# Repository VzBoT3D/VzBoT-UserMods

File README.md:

# VzBoT UserMods repository

Welcome to the VzBoT UserMods repository, here you may find community mods for the VzBoT 3D-printer.

*Remember to update this README when uploading new mod!*

There is a [contributing guide available here](./CONTRIBUTING.md).

## Directory structure

Create a folder containing your name (without spaces) and create a folder for your mod(s).

Suggested directory layout for your mod:
- creator_name/
  - mod_name/
    - README.md with a description, optionally build instructions and required parts
    - stl/ folder with stereolithographical models, oriented correctly for printing
    - cad/ folder with original design files (STEP, F3D, Scad, etc.) (optional)
    - doc/ folder with supported documentation (optional)
    - images/ folder with screen shots/renders/etc.

## Table structure

Update the following table with the information about your mod:
- Your name
- A link to your sub-folder
- A short description of your mod
- The build difficulty:
  - :green_heart: for :green_heart: (Easy)
  - :blue_heart: for :blue_heart: (Intermediate)
  - :heart: for :heart: (Advanced)

like so:
`
| Creator | [Mod title](link) | ✔️/✖️ | ✔️/✖️ | Description | Difficulty `

---

## Mods

| Creator | Mod title | Description | [Vz330](https://github.com/VzBoT3D/VzBoT-Vz330) | [Vz235](https://github.com/VzBoT3D/VzBoT-Vz235) | Difficulty
| --- | --- | --- | --- | --- | --- |
| example    | [Example mod](./creator_here/mod_folder_name)| Example entry for the table | ✔️ | ✔️ | :green_heart::blue_heart::heart: |
| airox    | [VZ235 Tophat](./airox/vz235_tophat)| A tophat for the vz235 | ✖️ | ✔️ | :green_heart: |
| AdderMk2   | [Patch_Cura](./AdderMk2/Patch_Cura) | Updates 2020 Tronxy profiles in Cura | ✔️ | ✔️ | :blue_heart: |
| CapnKrunchy | [Aluminum Z WAGO Mount](./CapnKrunchy/Aluminum_Z_WAGO_Mount) | WAGO mount for Aluminum Z bed assembly | ✔️ | ✖️ | :green_heart: |
| catalinutzz| [Hemera mount](./catalinutzz/hemera-mount) | Hemera mount for the VZ Printhead | ✔️ | ✔️ | :green_heart: |
| ckvsoft    | [CPAP_back_panel_tube_mount_VZ330](./ckvsoft/CPAP_back_panel_tube_mount_VZ330)| CPAP back panel tube mount VZ330. | ✔️ | ✖️ | :green_heart: |
| ckvsoft    | [WaveShare](./ckvsoft/waveshare_5inch_DSI_LCD)| WaveShare 5inch DSI LCD. | ✔️ | ✔️ | :green_heart: |
| der-pw    | [HBVCam-3M2111_corner-mount](./der-pw/HBVCam-3M2111_corner-mount)| HBVCam-3M2111 corner-mount | ✖️ | ✔️ | :green_heart: |
| edsped    | [Bowden Collet Adapter](./edsped/) | Bowden Collet Adapter  | ✔️ |  ✔️ | :green_heart: |
| EduardoMDSousa  | [Vz-Printhead Printed MGN12H](./EduardoMDSousa/Vz-Printhead-Printed-MGN12H) | VzPrinthead Printed MGN12H | ✔️ | ✔️ | :green_heart: |
|                 | [Vz-Printhead-Printed_Standoffs-MGN12](./EduardoMDSousa/Vz-Printhead-Printed_Standoffs-MGN12) | Vz-Printhead-Printed_Standoffs-MGN12 | ✔️ | ✔️ | :green_heart: |
|                 | [Vz-Printhead-Printed-MGN12H-Orbiter-1.5-Mood](./EduardoMDSousa/Vz-Printhead-Printed-MGN12H-Orbiter-1.5-Mood) | Vz-Printhead-Printed-MGN12H-Orbiter-1.5-Mood | ✔️ | ✔️ | :green_heart: |
| | [Vz-Printhead Printed Standoffs MGN12](./EduardoMDSousa/Vz-Printhead-Printed_Standoffs-MGN12) | Vz-Printhead Printed Standoffs MGN12 | ✔️ | ✔️ | :green_heart: |
|Glizzynator | [M4_Spool_Holder](./Glizzynator/M4_Spool_Holder)| Modifies the spool holder to use M4 screws instead of M3 | ✔️ | ✔️ | :green_heart: |
| jpbnto     | [Y endstop](./jpbnto/yendstop) | Y-endstop using the Tronxy XS5A switch | ✔️ | ✖️ | :green_heart: |
| | [VzHextrudort heavy back plate](./jpbnto/vzhextrudort_heavy_back_plate) | Y-endstop using the Tronxy XS5A switch | ✔️ | ✖️ | :green_heart: |
| jurisv      | [SLA CPAP Trihorn](./jurisv/sla_cpap_trihorn)                             | CPAP Trihorn Fan ducts for SLA printers as single piece          | ✔️ | ✖️ | :green_heart: |
| karnadi    | [NF Crazy front face](./karnadi/NF_Crazy_2510_BLTouch) | NF Crazy front face 2510 fan with BLTouch mount | ✔️ | ✔️ | :green_heart: |
|            | [VzHextrudort pneumatic coupler](./karnadi/VzHextrudort_pneumatic_coupler) | VzHextrudort pneumatic PTFE coupler | ✔️ | ✔️ | :green_heart: |
| keefo      | [vent hose adapter](./keefo/vent_hose_adapter) | vent hose adapter | ✔️ | ✖️ | :green_heart: |
| knarfie    | [12mm Linear Rod](./knarfie/12mm_rods) | Mod for 12mm linear rods | ✔️ | ✖️ | :green_heart: |
|            | [Idler Shoulder](./knarfie/shoulder_idler) | Idler mounts with spots for shoulder bolts  | ✔️ | ✖️ | :green_heart: |
|            | [Trihorn](./knarfie/trihorn_duct) | Trihorn duct for the VZ Printhead | ✔️ | ✔️ | :green_heart: |
| MadduxVape | [Vz330 Duet Config](./MadduxVape) | Vz330 AWD Config for Duett board| ✔️ |  ✖️ | :green_heart: |
| marbocub   | [Vz330 Y-Gantry-1515](./marbocub/Vz330_Y-Gantry-1515) | Vz330 Y-Gantry for 1515 size gantry | ✔️ |  ✖️ | :green_heart: |
| mdwasp     | [Swappable Exhaust Tube](./mdwasp/swappable_exhaust_tube) | Hot-swappable exhaust tube | ? | ✔️ | :green_heart: |
| panik988   | [Sherpa + NF Crazy front face (bracket)](./panik988/sherpa_nf_crazy_bracket) | NF Crazy Face Mount with bracket for Sherpa | ✔️ | ✔️ | :green_heart: |
| pbsuper    | [VZTrident](./pbsuper/VZTrident)| Tripple Z for VZbot complete printer. | ✔️ | ✔️ | :blue_heart: |
|            | [Quickdraw](./pbsuper/Quickdraw)| Quickdraw for Alu Printhead. | ✔️ | ✔️ | :green_heart: |
|            | [Brace_Dancer](./pbsuper/Brace_Dancer)| Brace for Dancer so Fanduct can't move sideways. | ✔️ | ✔️ | :green_heart: |
| Polar_Ted  | [VZ HextrudORT mount](./Polar_Ted/VZ_HextrudORT_High_Motor_Mount_for_EVA/) | VZ HextrudORT high motor mount for EVA print head and V6 hot end | ✔️ |  ✔️ | :green_heart: |
|            | [VZ Sexbolt Z Endstop](./Polar_Ted/Sexbolt_Sidepiece_Z_Switch/) | Sexbolt side mounted Z endstop for VZ bed frame  | ✔️ |  ✔️ | :green_heart: |
|            | [VZ 330 Skirt Set](./Polar_Ted/VZ330_skirt/ ) | VZ 3330 SKirt Set with V0 Display | ✔️ | ✖️ | :green_heart: |
|            | [X_Y_Pully_Height_Gauge](./Polar_Ted/X_Y_Pully_Height_Gauge/) | X Y pully height gauge  | ✔️ |  ✔️ | :green_heart: |
|            | [X_Y Motor Support](./Polar_Ted/X_Y_Motor_support/) | Support shelf for X and Y motors  | ✔️ |  ✔️ | :green_heart: |
| Rac        | [MGN9 Gantry](./Rac/MGN9_gantry) | MGN9 gantry | ✔️ | ✔️ | ✖️ | :blue_heart: |
| rilmar     | [X5SA Z](./rilmar/X5SA_Z) | X5SA Z | ✔️ | ✔️ | :green_heart: |
| RODAM 3D   | [180_Hinges](./RODAM_3D/180_Hinges/) | 180 Hinges for full door open  | ✖️ |  ✔️ | :green_heart: |
|            | [2WD_2_COLOR_SCREW_PACK](./RODAM_3D/2WD_2_COLOR_SCREW_PACK/) | 2 color Idler with mod for screw kit  | ✖️ |  ✔️ | :green_heart: |
| SFINAE     | [Rapido HF mount](./SFINAE/Rapido_HF_30mm_fan) | Rapido HF mount for 30mm fan | ✔️ | ✔️ | :green_heart: |
| Skysi      | [Beefy X-Endstop](./Skysi/Beefy%20X-Endstop) | Beefed up Enstop for X | ✔️ | ✔️ | :green_heart: |
| SSerpente  | [Klicky probe](./SSerpente/Klicky%20probe%20Vzbot) | Klicky probe mount | ✔️ | ✔️ | :green_heart: |
| treintjes  | [Skirt](./treintjes/VzBot_Skirt) | Skirt for the VZ-Bot to house electronics under the frame | ✔️ |  ✖️ | :green_heart: |
| MadduxVape | [Vz330_Duet_Config](./MadduxVape) | Vz330 AWD Config for Duett board| ✔️ |  ✖️ | :green_heart: |
| zxzimeng  | [12mm rod aligner](./zxzimeng/12mm_aligner/) | 12mm Z Rod Aligner  | ✖️ |  ✔️ | :green_heart: |
| Lobod     | [VzHextrudORT Optical Filament Sensor](./Lobod/VzHextrudORT_Filament-Sensor/) | Optical Filament sensor for printed VzHextrudORT | ✔️ | ✔️ | :heart: |

<sub>Credits to [VoronDesign/VoronUsers](https://github.com/VoronDesign/VoronUsers)</sub>

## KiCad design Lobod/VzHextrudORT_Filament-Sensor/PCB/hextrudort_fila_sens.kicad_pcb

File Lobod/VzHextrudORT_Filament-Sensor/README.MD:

# Better filament sensor for VzHextrudORT

Based on ERCF Binky and has the same BOM.
Uses similar principle as hall effect filament sensor, but utilizes optical path blocking for triggering.

# BOM
The same as in the original Extruder **except 6x3mm magnet**

# PCB BOM
| Component | Symbol  | Footprint |
|-----------|:--------|:----------|
Capacitor 0.1µF|C2|0603
Resistor 10K|R1|0603
Resistor 1K|R2|0603
Resistor 330R|R3|0603
LED Diode|D1|1206
EE-SX1103|IC1|EESX1103
SN74LVC1G14DBVR|IC1|SOT95P280X145-5N
JST PH 3pin|J1|JST_PH_B3B-PH-K_1x03_P2.00mm_Vertical

Interactive BOM can be found in ./PCB/BOM/ibom.html

# Build
1. Order PCB from a manufacturer.
    Ones I have tested in the past: OSHPark, JLCPCB, PcbWay.

2. Solder all parts to their coresponding places (for now there is no possibility to get soldered sensors).

3. Print included STLs (You may use supports in magnet section).

4. Place 6x3mm Magnet in the printed slot.

5. Press fit sensor into the printed base.

6. Enjoy!

# PCB Images

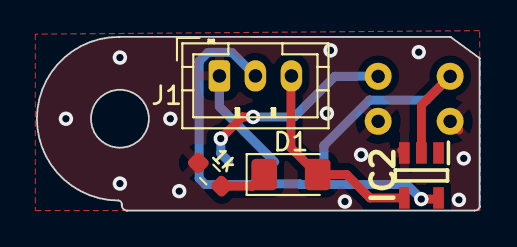
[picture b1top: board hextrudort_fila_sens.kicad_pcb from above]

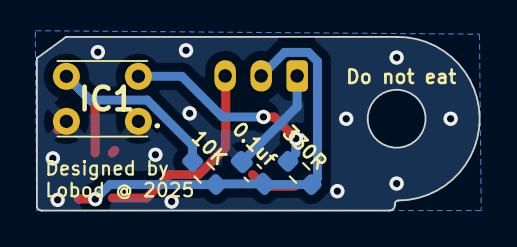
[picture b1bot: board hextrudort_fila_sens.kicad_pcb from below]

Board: 2 copper layers, 24.6 x 9.6 mm, 8 parts (4 on the bottom side), 6 nets.

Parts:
C2: 0.1uf; C_0603_1608Metric_Pad1.08x0.95mm_HandSolder
D1: LED; LED_1206_3216Metric_Pad1.42x1.75mm_HandSolder
IC1: EE-SX1103; EESX1103
IC2: SN74LVC1G14DBVR; SOT95P280X145-5N
J1: Conn_01x03; JST_PH_B3B-PH-K_1x03_P2.00mm_Vertical
R1: 10K; R_0603_1608Metric_Pad0.98x0.95mm_HandSolder
R2: 1k; R_0603_1608Metric_Pad0.98x0.95mm_HandSolder
R3: 330R; R_0603_1608Metric_Pad0.98x0.95mm_HandSolder

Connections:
+5V: C2.1, IC2.5 (VCC), J1.2, R1.2, R3.1
/SIG: D1.2 (A), IC2.4 (Y), J1.3
GND: C2.2, IC1.1 (K), IC1.4 (E), IC2.3 (GND), J1.1, R2.2
unnamed: D1.1 (K), R2.1
unnamed: IC1.2 (A), R3.2
unnamed: IC1.3 (C), IC2.2 (A), R1.1

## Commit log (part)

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2022-04-17 Adding options
2022-04-17 Added Magnet ball option
2022-04-17 Added Quickdraw
2022-04-23 Added quickdraw seperate
2022-04-23 Quickdraw has it's own repository. (#20)
2022-04-23 Probe_mount
    Quickdraw_mount for printed printhead version. and Picture added how to assemble Dock
2022-04-27 initial commit WaveShare 5inch DSI LCD
2022-04-27 add image
2022-04-28 VZ_HextrudORT_High_Motor_Mount_for_EVA (#18)
    * Create README.md
    * Add files via upload
    * Update README.md
2022-04-28 WaveShare 5inch DSI LCD (#21)
    * initial commit WaveShare 5inch DSI LCD
    * add image
    * update README.md
2022-05-12 ordening
2022-05-17 rechange
2022-05-17 please (#28)
2022-05-17 VZ Sexbolt Z endstop (#22)
2022-05-17 Create mods
2022-05-17 Create description
2022-05-17 Rename description to ReadMe
2022-05-17 adding Yendstop.stl (#29)
    * Create mods
    * Add files via upload
    * Delete mods
    * Create description
    * Rename description to ReadMe
    * Update ReadMe
2022-05-18 Adding Y endstop photo
2022-05-18 adding yendstop photo
2022-05-18 adding yendstop photo (#30)
    * Create mods
    * Add files via upload
    * Delete mods
    * Create description
    * Rename description to ReadMe
    * Update ReadMe
2022-05-18 Moved the yendstop to its own folder
2022-05-18 Link to Vz235
2022-05-20 organise
2022-05-27 Adding Pully gauge and motor support shelf (#31)
2022-06-05 Created the folder and the README file
2022-06-05 added the .stl files and slicer pics
2022-06-05 added a pic
2022-06-16 Clamp for 5015
2022-06-26 Commit From desktop app
    Re trying a commit from the desktop app windows
2022-06-27 Changed image naming
    I've changed the naming of the images to avoid possible illegals characters
2022-06-27 Change smaller stl name
2022-06-27 Hading 180 door hinges MOD (Take 2)
    I had so many fail on my firs sync. I just deleted my first fork and this is the second try at making contribution !!!!
2022-06-27 Relocated the readme file in the folder
    OUPS! the readme file was on the first level. now it's in the folder of the mod itself!
2022-06-29 Add tophat
2022-06-29 Add to README
2022-07-02 Add files via upload
    Changed hole position for the cf tube, was 0.5mm off
2022-07-02 Endstop for MGN9 on Y
2022-07-03 Change orientation of STL Files
    Change orientation to conform to print orientation.
2022-07-06 Add tophat for vz235 (#36)
2022-07-06 Hading 180 door hinges MOD (Take 2) (#35)
2022-07-26 Had step files for Hinges
2022-08-27 Create Readme for swappable exhaust
2022-08-27 Add mdwasp/hot swappable exhaust tube
2022-08-27 Enlarge cutout for cable channel
2022-09-16 VZ330 Skirts with V0 display (#39)
2022-09-16 Added brace for Dancer so 5015 can't move (#33)
2022-09-16 Add hot swappable exhaust adapter (#38)
    * Add mdwasp/hot swappable exhaust tube
    * Enlarge cutout for cable channel
2022-09-16 New parts And pic (#37)
    * Hading 180 door hinges MOD (Take 2)
    I had so many fail on my firs sync. I just deleted my first fork and this is the second try at making contribution !!!!
    * Relocated the readme file in the folder
    OUPS! the readme file was on the first level. now it's in the folder of the mod itself!
    * Change orientation of STL Files
    Change orientation to conform to print orientation.
2022-09-16 Adding the Beefy X-Endstop mod (#32)
2022-09-17 QD2 cpap
2022-09-17 Update for Quickdraw and VZK235 and VZK330 (#41)
2022-10-03 Sherpa NF Crazy by Mellow with bracket (#42)
2022-10-03 Renamed to match table
2022-10-22 CPAP back panel tube mount VZ330
2022-10-22 CPAP back panel tube mount VZ330 outlet
2022-10-22 Update README.md
    add CPAP_back_panel_tube_mount_VZ330
2022-10-24 CPAP back panel tube mount VZ330 (#43)
2022-12-20 New Quickdraw version.
    New QD2 due to bed mesh issue's with old.
2023-01-07 Goliath version.
2023-01-09 Added Aluminum Z WAGO Mount
2023-01-09 Add CAD, STLs, and Images
2023-01-09 Add Aluminum Z WAGO Mount
2023-01-09 Rename mod folder to remove spaces
2023-01-09 Fix rename error
2023-01-10 Organizing
2023-01-21 upload .step
2023-01-26 CPAP one piece resin fan ducts
2023-02-07 Update README.md
    Small text correction, add thanks
2023-02-07 Delete trihorn spacer For Rapido MGN12H.3mf
    eliminar
    trihorn spacer For Rapido MGN12H.3mf
    error in dimensions
2023-02-07 Delete trihorn spacer For Rapido MGN12H.stl
    eliminar
    trihorn spacer For Rapido MGN12H.stl
    error in dimensions
2023-02-07 Add files via upload
    add , trihorn spacer For Rapido MGN12H V2.stl , with corrected stanoff measurements
2023-02-07 Add files via upload
    add step V2 with, trihorn spacer For Rapido MGN12H V2 , with corrected stanoff measurement
2023-02-07 Delete Cariage mgn12 Extra parts.step
    delete outdated step
2023-02-07 Add files via upload
    Add image Vzbot_printe_head_MGN12H_Cariage mgn12 Extra parts.png
2023-02-07 Add files via upload
    Add readme to Cad Cariage mgn12 Extra parts
2023-02-07 Update README.md
    image link correction
2023-02-08 Create Klicky_Trihorn Fan Duct v2.stl
    Add stl Trihorn Duct with Klicky probe dock under
    printed , and tested
2023-02-11 Update folder and image for klicky duct
    update
    add Klicky_Trihorn Fan Duct v2 readme
    add klicky image galery for readme
2023-02-11 Update image liks
2023-02-11 update image size
2023-02-11 update image links 2
2023-02-26 Delete Klicky_Trihorn Fan Duct v2.stl
    New v3 uplouded
2023-02-26 Add files via upload
    Vew vertion
    change on magnet hight
2023-02-28 New Mount for Vz235.
2023-03-06 add how to images
2023-03-06 edit readme with how to image and resize images
2023-03-06 edit readmi
    add how to image and reorganize page images and positions for better look
2023-03-06 add soldering magntes option
    Klicky_Trihorn Fan Duct v3 solder magn v1.stl
2023-03-12 Create Duet Wifi + Duex FIrmware
2023-03-12 Update and rename Duet Wifi + Duex FIrmware to Duet Wifi + Duex readme
2023-03-12 Rename Duet Wifi + Duex readme to README.md
2023-03-20 Vz-Printhead-Printed_Standoffs-MGN12_mood
    Add plastic standoffs vertion of the MGN12 Mood
2023-03-20 add print head pic
    2 pics missing
2023-03-20 Update README.md
    Readmi for Vz-Printhead-Printed Printed-Standoffs-MGN12 Mood
2023-03-20 Add files via upload
    Missin M3 self lock nut pic
2023-03-20 Add files via upload
    missing m3 x 45 bolt image
2023-03-20 Update README.md
    edit Bom hardware readme
2023-03-20 Update README.md
    edit readmi add pics and rework
2023-03-20 Update README.md
    Add Vz-Printhead-Printed_Standoffs-MGN12 Mood
2023-03-21 Update README.md
    edit readmi to correct erros on cli
2023-03-21 Add files via upload
    add redy all parts bed plate stl
2023-03-21 Add files via upload
    add print orienation buid plate pic
2023-03-21 Update README.md
    edit description with pic for buid plate orientation and stl of all parts
2023-03-23 Delete All Parts MGN12 (plastc standoffs).stl
    rong arage of front standoffs
2023-03-23 Add files via upload
    new correted stl of all plarts on table
2023-03-23 Update README.md
    edit missing links
2023-03-23 Update README.md
    correcting links
2023-03-24 Update README.md
    change mood for the correct name
2023-03-24 Update README.md
    update mood link
2023-04-02 Create Rat Rig to VzBot wire raceway
2023-04-07 Restructuring Folders
2023-04-26 Adding batch mood Vz-Printhead-Printed_Standoffs-MGN12 (#48)
    * Vz-Printhead-Printed_Standoffs-MGN12_mood
    Add plastic standoffs vertion of the MGN12 Mood
    * add print head pic
    2 pics missing
    * Update README.md
    Readmi for Vz-Printhead-Printed Printed-Standoffs-MGN12 Mood
2023-04-26 X5SA Z Axis component Reuse (#51)
2023-04-27 Add files via upload
    my vzhextrudort is using BMG clone gears. spacing will be different with the original BMG gears
2023-04-27 added vzhextrudort heavy backplate (#52)
    * Create mods
    * Add files via upload
    * Delete mods
    * Create description
    * Rename description to ReadMe
    * Update ReadMe
2023-04-27 Tidy
2023-04-28 Create sensore filamento per vz extruder stampato
2023-05-12 adding HBVCam-3M2111_corner-mount
2023-05-12 Update readme.md
    small typos
2023-06-17 Update Readme.md
    New Dockable probe repo with better code.
2023-06-17 Update Readme.md (#55)
2023-06-17 removed unnecesary files
2023-06-17 removing more stuff.
2023-06-17 even more files removed.
2023-07-29 Update README.md
    Edite redadme
    beta untested tp tested
2023-07-29 Create Vz-Printhead-Print-MGN12H-Orbiter-1.5-Mood
    Create Vz-Printhead-Printed-MGN12H-Orbiter-1.5-Mood
    back plate and orbiter 1.5 adapter plate for Vz-Printhead-Printed-MGN12H
2023-07-29 Update README.md
    Add new mood
    | EduardoMDSousa | [Vz-Printhead-Printed-MGN12H-Orbiter-1.5-Mood](./EduardoMDSousa/Vz-Printhead-Printed-MGN12H-Orbiter-1.5-Mood) | Vz-Printhead-Printed-MGN12H-Orbiter-1.5-Mood | ✔️ | ✔️ | :green_hear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
2023-07-29 Add Cad folder
    Add missing cad floder
2023-07-29 add image folder
    Add image folder to try solve the conflict
2023-08-25 add Vz330 Y-Gantry-1515
2023-09-18 File was an image
2023-10-05 Added M4 spool holder mod
2023-11-30 Update Readme.md (#66)
2023-12-14 Create Fan Duct
2023-12-14 Create klicky-00
2023-12-14 Create klicky-00_duct
2023-12-14 Rename klicky-00 duct.stl to klicky-00_duct.stl
2024-02-19 klicky-00 (#67)
2024-02-19 Update Readme.md (#63)
2024-02-19 files cleaned up. (#58)
2024-02-19 Create Rat Rig to VzBot wire raceway (#49)
2024-03-03 Create Vz-Printhead-Printed-MGN12H-Orbiter-1.5-Mood (#61)
    * Vz-Printhead-Printed_Standoffs-MGN12_mood
    Add plastic standoffs vertion of the MGN12 Mood
    * add print head pic
    2 pics missing
    * Update README.md
    Readmi for Vz-Printhead-Printed Printed-Standoffs-MGN12 Mood
2024-07-05 Create CAD
2024-07-05 Create keep
2024-07-05 Create . …
2024-07-08 Update README.md
    change pic link
2024-08-27 add vent hose adapter
2024-08-27 add a image
2024-12-27 Create README.md 12mm Rod Aligner
2024-12-27 12mm aligner fifles
2024-12-27 Update README.md 12mm Z Rod Aligner
2024-12-27 Rename 12mm_aligner_CAD picture.png to 12mm_aligner_CAD_picture.png
2024-12-27 Rename 12mm aligner.stl to 12mm_aligner.stl
2025-01-10 Rename Bowden Clip Adapter.jpg to Bowden Clip Adapter.jpg
2025-01-10 Rename Image2.jpg to image2.jpg
2025-01-10 Rename image.jpg to image.jpg
2025-01-10 Rename bowden_clip-big.3mf to bowden_clip-big.3mf
2025-01-10 Rename bowden_clip-big.stl to bowden_clip-big.stl
2025-01-10 Rename bowden_clip-small.3mf to bowden_clip-small.3mf
2025-01-10 Rename bowden_clip-small.stl to bowden_clip-small.stl
2025-01-10 Rename readme.md to readme.md
2025-01-10 Rename Bowden Clip Adapter.jpg to Bowden-Clip_Adapter.jpg
2025-01-10 Rename edsped/Bowden_Adapter/Bowden-Clip_Adapter.jpg to edsped/Bowden_Adapter/docs/Bowden-Clip_Adapter.jpg
2025-01-10 Rename edsped/Bowden_Adapter/image.jpg to edsped/Bowden_Adapter/docs/image.jpg
2025-01-10 Rename edsped/Bowden_Adapter/image2.jpg to edsped/Bowden_Adapter/docs/image2.jpg
2025-01-10 Rename edsped/Bowden_Adapter/bowden_clip-big.stl to edsped/Bowden_Adapter/stl/bowden_clip-big.stl
2025-07-26 VzHextrudORT Filament Sensor
